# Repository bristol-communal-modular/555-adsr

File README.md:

# 555 ADSR Envelope

An ADSR envelope we've built for our eurorack systems.

This version is based on the schematic from Yves Usson at [YuSynth](https://www.yusynth.net/Modular/modular.html).
More information on it is available from the [relevant page on his site](https://www.yusynth.net/Modular/EN/ADSR/index_latest.html).

## Contact

Drop us an email at bristolcommunalmodular at gmail.com

## License

The files in this project are shared under an [Attribution-NonCommercial-ShareAlike 4.0 International License](https://creativecommons.org/licenses/by-nc-sa/4.0/)

This means that you can share the info here around, and transform or build upon the circuits and designs in here, as long as you share anything you do under the same license and give BCM and YuSynth a shout-out.

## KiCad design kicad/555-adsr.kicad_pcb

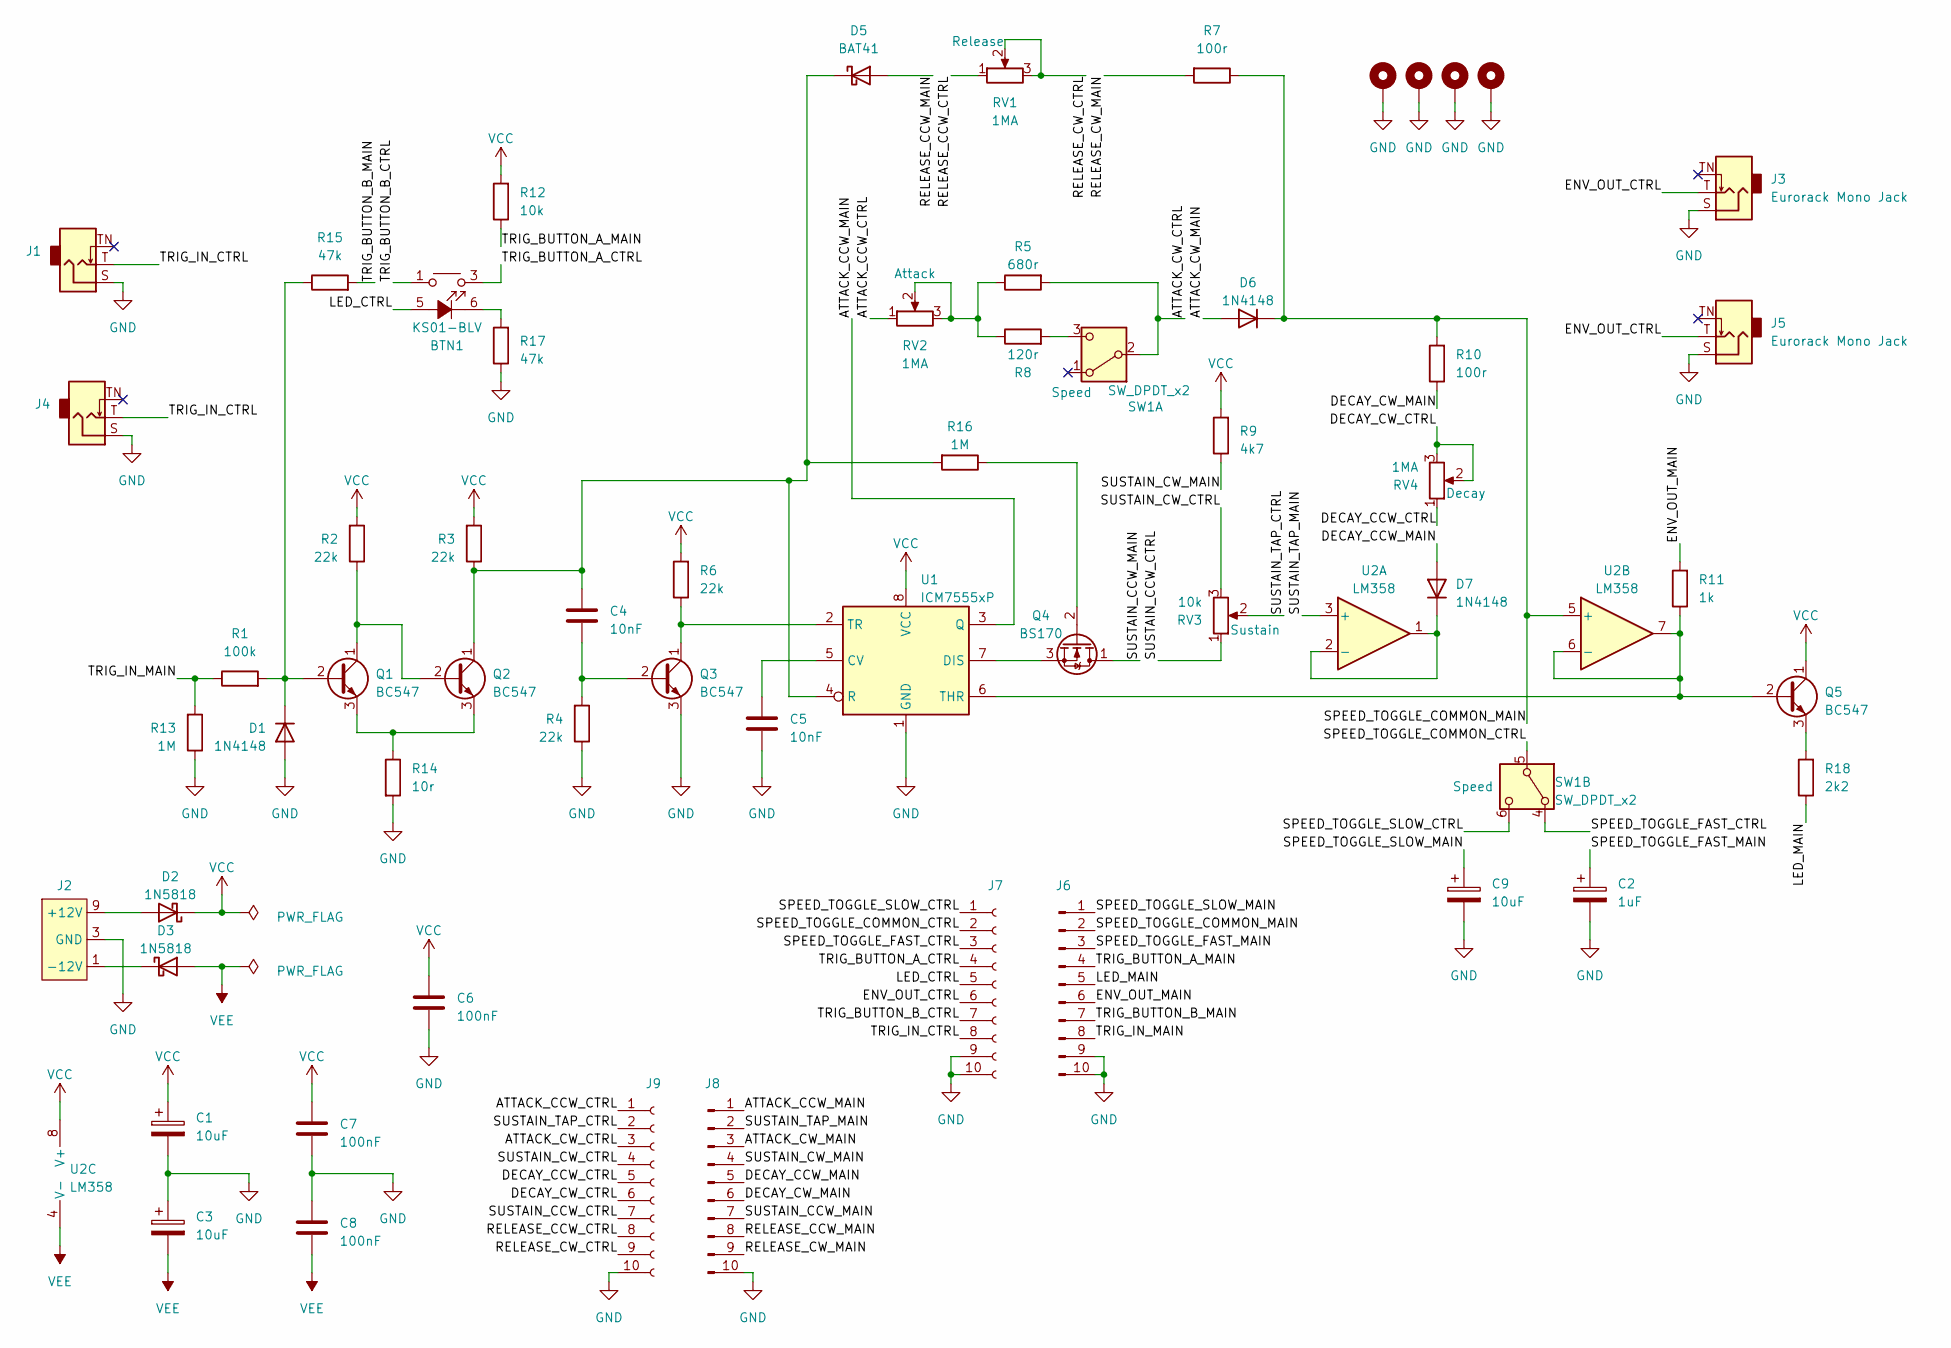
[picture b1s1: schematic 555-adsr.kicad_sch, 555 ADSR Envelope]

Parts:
BTN1: KS01-BLV
C1, C3, C9: 10uF; CP_Radial_D5.0mm_P2.00mm
C2: 1uF; CP_Radial_D5.0mm_P2.00mm
C4, C5: 10nF; C_Rect_L7.0mm_W2.5mm_P5.00mm
C6, C7, C8: 100nF; C_Rect_L7.0mm_W2.5mm_P5.00mm
D1, D6, D7: 1N4148; D_DO-35_SOD27_P7.62mm_Horizontal
D2, D3: 1N5818; D_DO-41_SOD81_P10.16mm_Horizontal
D5: BAT41; D_DO-35_SOD27_P7.62mm_Horizontal
H1, H2, H3, H4: MountingHole_Pad; MountingHole_3.2mm_M3_DIN965_Pad
J1, J3, J4, J5: Eurorack Mono Jack; Jack_3.5mm_QingPu_WQP-PJ398SM_Vertical; mpn WQP-WQP518MA
J2: Eurorack Power Small; Eurorack_PowerHeader_2x05_P2.54mm_Shrouded
J6, J8: Conn_01x10_Pin; PinHeader_1x10_P2.54mm_Vertical
J7, J9: Conn_01x10_Socket; PinSocket_1x10_P2.54mm_Vertical
Q1, Q2, Q3, Q5: BC547; TO-92_Inline_Wide
Q4: BS170; TO-92_Inline_Wide
R1: 100k; R_Axial_DIN0207_L6.3mm_D2.5mm_P10.16mm_Horizontal; Tolerance 1%
R2, R3, R4, R6: 22k; R_Axial_DIN0207_L6.3mm_D2.5mm_P10.16mm_Horizontal; Tolerance 1%
R5: 680r; R_Axial_DIN0207_L6.3mm_D2.5mm_P10.16mm_Horizontal; Tolerance 1%
R7, R10: 100r; R_Axial_DIN0207_L6.3mm_D2.5mm_P10.16mm_Horizontal; Tolerance 1%
R8: 120r; R_Axial_DIN0207_L6.3mm_D2.5mm_P10.16mm_Horizontal; Tolerance 1%
R9: 4k7; R_Axial_DIN0207_L6.3mm_D2.5mm_P10.16mm_Horizontal; Tolerance 1%
R11: 1k; R_Axial_DIN0207_L6.3mm_D2.5mm_P10.16mm_Horizontal; Tolerance 1%
R12: 10k; R_Axial_DIN0207_L6.3mm_D2.5mm_P10.16mm_Horizontal; Tolerance 1%
R13, R16: 1M; R_Axial_DIN0207_L6.3mm_D2.5mm_P10.16mm_Horizontal; Tolerance 1%
R14: 10r; R_Axial_DIN0207_L6.3mm_D2.5mm_P10.16mm_Horizontal; Tolerance 1%
R15, R17: 47k; R_Axial_DIN0207_L6.3mm_D2.5mm_P10.16mm_Horizontal; Tolerance 1%
R18: 2k2; R_Axial_DIN0207_L6.3mm_D2.5mm_P10.16mm_Horizontal; Tolerance 1%
RV1, RV2, RV4: 1MA; Potentiometer_Alpha_RD901F-40-00D_Single_Vertical
RV3: 10k; Potentiometer_Alpha_RD901F-40-00D_Single_Vertical
SW1: SW_DPDT_x2; SW_DPDT_DailyWell_MiniToggle
U1: ICM7555xP; DIP-8_W7.62mm_Socket
U2: LM358; DIP-8_W7.62mm_Socket

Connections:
/ATTACK_CCW_CTRL: J9.1, RV2.1
/ATTACK_CCW_MAIN: J8.1, U1.3 (Q)
/ATTACK_CW_CTRL: J9.3, R5.2, SW1.2 (B)
/ATTACK_CW_MAIN: D6.2 (A), J8.3
/DECAY_CCW_CTRL: J9.5, RV4.1
/DECAY_CCW_MAIN: D7.2 (A), J8.5
/DECAY_CW_CTRL: J9.6, RV4.2, RV4.3
/DECAY_CW_MAIN: J8.6, R10.1
/ENV_OUT_CTRL: J3.T, J5.T, J7.6
/ENV_OUT_MAIN: J6.6, R11.2
/LED_CTRL: BTN1.5 (A), J7.5
/LED_MAIN: J6.5, R18.1
/RELEASE_CCW_CTRL: J9.8, RV1.1
/RELEASE_CCW_MAIN: D5.2 (A), J8.8
/RELEASE_CW_CTRL: J9.9, RV1.2, RV1.3
/RELEASE_CW_MAIN: J8.9, R7.2
/SPEED_TOGGLE_COMMON_CTRL: J7.2, SW1.5 (B)
/SPEED_TOGGLE_COMMON_MAIN: D6.1 (K), J6.2, R7.1, R10.2, U2.5 (+)
/SPEED_TOGGLE_FAST_CTRL: J7.3, SW1.4 (A)
/SPEED_TOGGLE_FAST_MAIN: C2.1, J6.3
/SPEED_TOGGLE_SLOW_CTRL: J7.1, SW1.6 (C)
/SPEED_TOGGLE_SLOW_MAIN: C9.1, J6.1
/SUSTAIN_CCW_CTRL: J9.7, RV3.1
/SUSTAIN_CCW_MAIN: J8.7, Q4.1 (D)
/SUSTAIN_CW_CTRL: J9.4, RV3.3
/SUSTAIN_CW_MAIN: J8.4, R9.1
/SUSTAIN_TAP_CTRL: J9.2, RV3.2
/SUSTAIN_TAP_MAIN: J8.2, U2.3 (+)
/TRIG_BUTTON_A_CTRL: BTN1.3, BTN1.4, J7.4
/TRIG_BUTTON_A_MAIN: J6.4, R12.1
/TRIG_BUTTON_B_CTRL: BTN1.1, BTN1.2, J7.7
/TRIG_BUTTON_B_MAIN: J6.7, R15.2
/TRIG_IN_CTRL: J1.T, J4.T, J7.8
/TRIG_IN_MAIN: J6.8, R1.1, R13.2
GND: C1.2, C2.2, C3.1, C5.1, C6.1, C7.1, C8.2, C9.2, D1.2 (A), H1.1, H2.1, H3.1, H4.1, J1.S, J2.3 (GND), J2.4 (GND), J2.5 (GND), J2.6 (GND), J2.7 (GND), J2.8 (GND), J3.S, J4.S, J5.S, J6.9, J6.10, J7.9, J7.10, J8.10, J9.10, Q3.3 (E), R4.1, R13.1, R14.2, R17.1, U1.1 (GND)
unnamed: BTN1.6 (K), R17.2
unnamed: D1.1 (K), Q1.2 (B), R1.2, R15.1
unnamed: D2.2 (A), J2.9 (+12V), J2.10 (+12V)
unnamed: D3.1 (K), J2.1 (-12V), J2.2 (-12V)
unnamed: C4.1, D5.1 (K), Q2.1 (C), R3.1, R16.2, U1.4 (R)
unnamed: D7.1 (K), U2.1, U2.2 (-)
unnamed: Q1.1 (C), Q2.2 (B), R2.1
unnamed: Q1.3 (E), Q2.3 (E), R14.1
unnamed: C4.2, Q3.2 (B), R4.2
unnamed: Q3.1 (C), R6.1, U1.2 (TR)
unnamed: Q4.2 (G), R16.1
unnamed: Q4.3 (S), U1.7 (DIS)
unnamed: Q5.2 (B), R11.1, U1.6 (THR), U2.6 (-), U2.7
unnamed: Q5.3 (E), R18.2
unnamed: R5.1, R8.1, RV2.2, RV2.3
unnamed: R8.2, SW1.3 (C)
unnamed: C5.2, U1.5 (CV)
VCC: C1.1, C6.2, C7.2, D2.1 (K), Q5.1 (C), R2.2, R3.2, R6.2, R9.2, R12.2, U1.8 (VCC), U2.8 (V+)
VEE: C3.2, C8.1, D3.2 (A), U2.4 (V-)

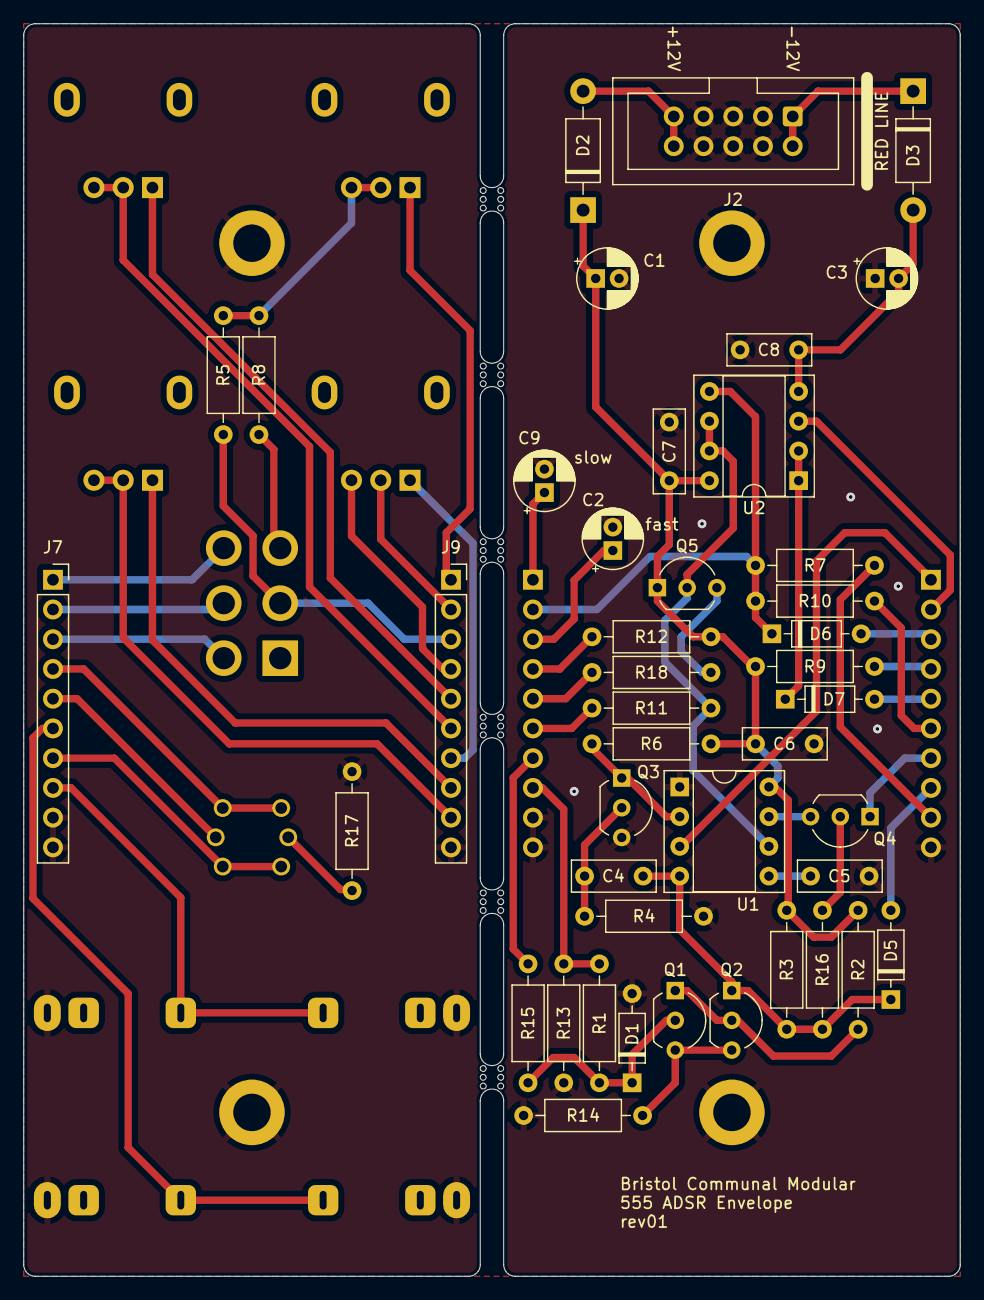
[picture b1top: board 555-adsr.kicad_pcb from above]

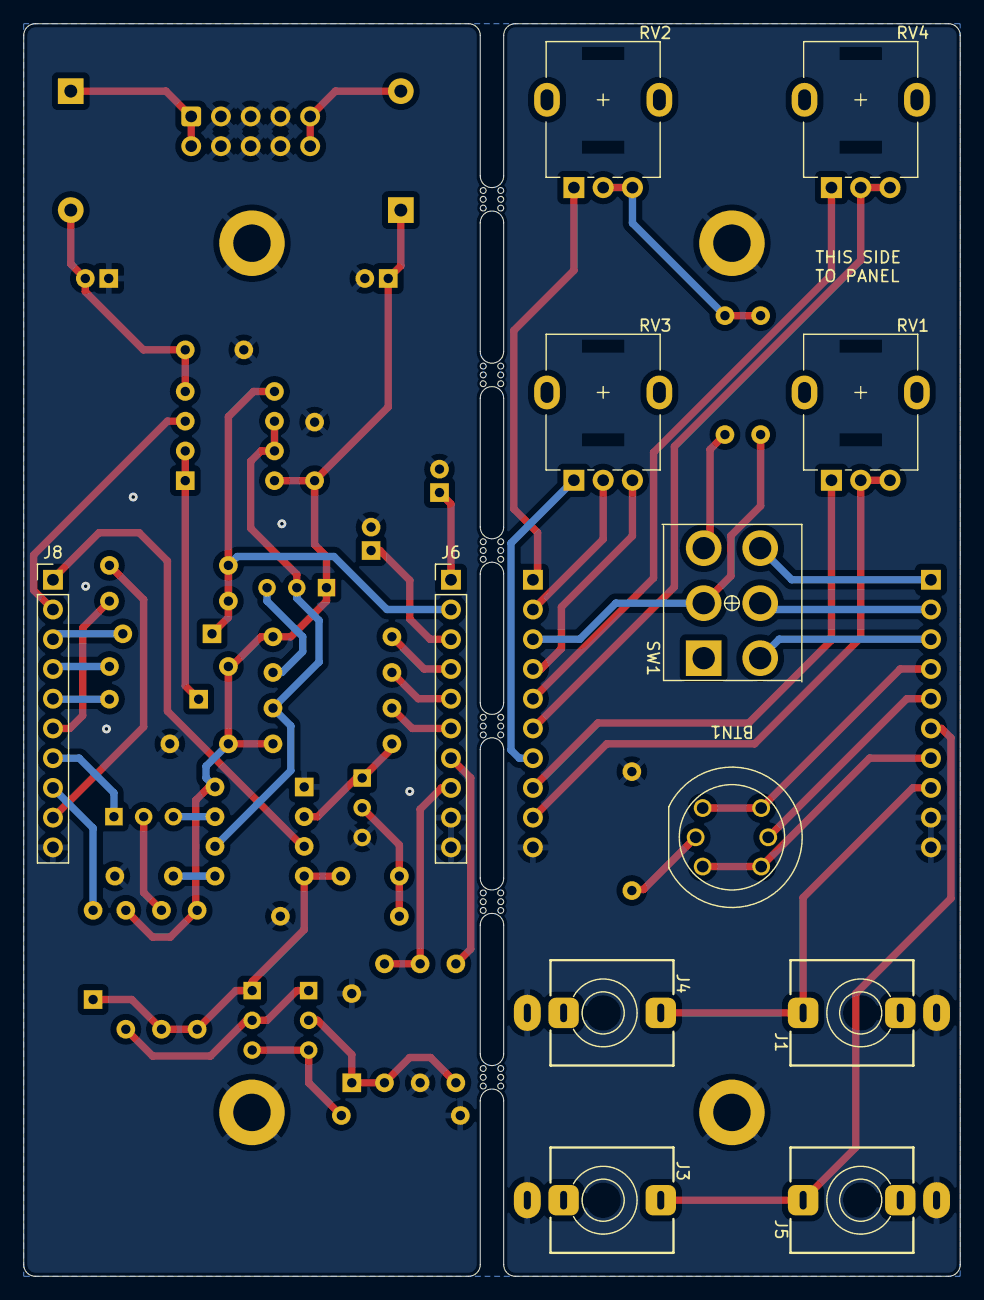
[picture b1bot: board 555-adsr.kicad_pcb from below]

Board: 2 copper layers, 80.0 x 107.0 mm, 65 parts (12 on the bottom side), 54 nets.

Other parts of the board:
mouse-bite-2mm-slot, mouse-bite-2mm-slot#2, mouse-bite-2mm-slot#3, mouse-bite-2mm-slot#4, mouse-bite-2mm-slot#5, mouse-bite-2mm-slot#6: VAL**; mouse-bite-2mm-slot

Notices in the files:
kicad/555-adsr.kicad_pcb:
creativecommons.org/licenses/by/4.0
License: CC BY 4.0
